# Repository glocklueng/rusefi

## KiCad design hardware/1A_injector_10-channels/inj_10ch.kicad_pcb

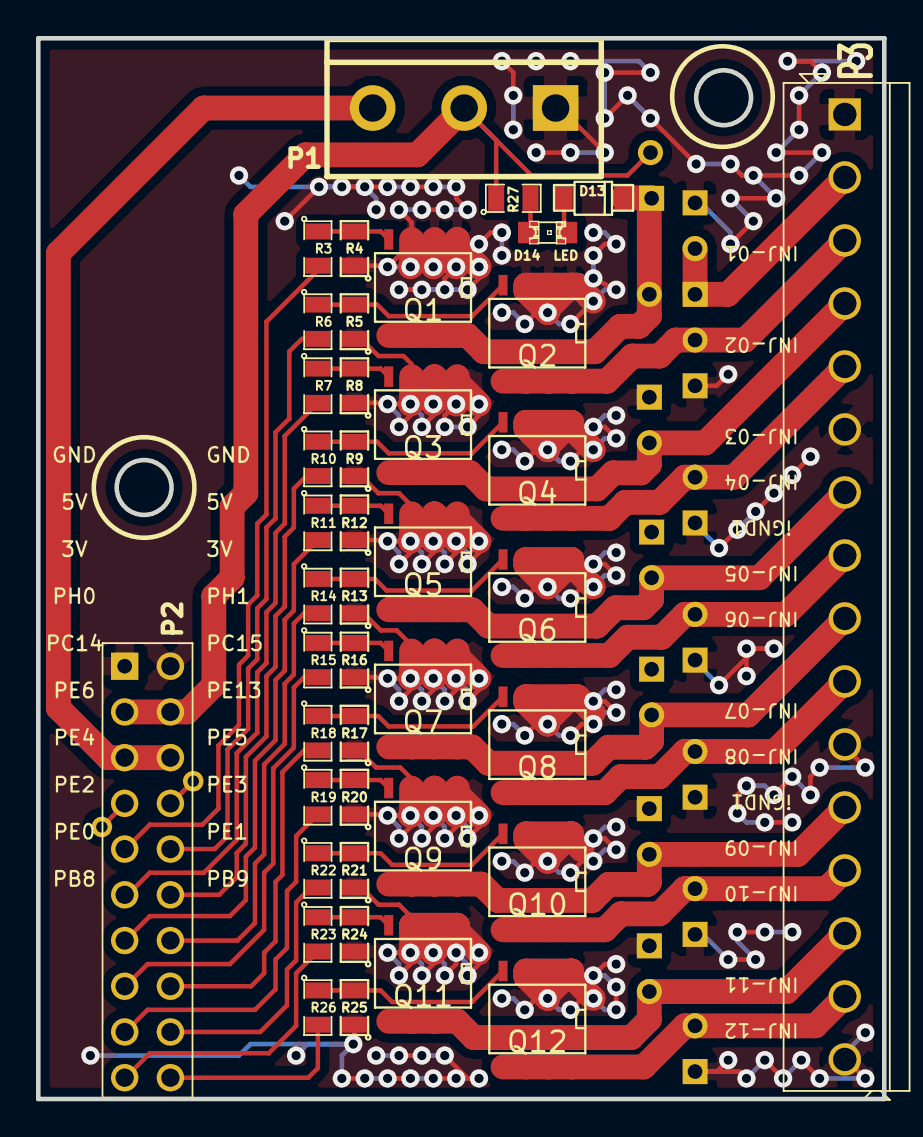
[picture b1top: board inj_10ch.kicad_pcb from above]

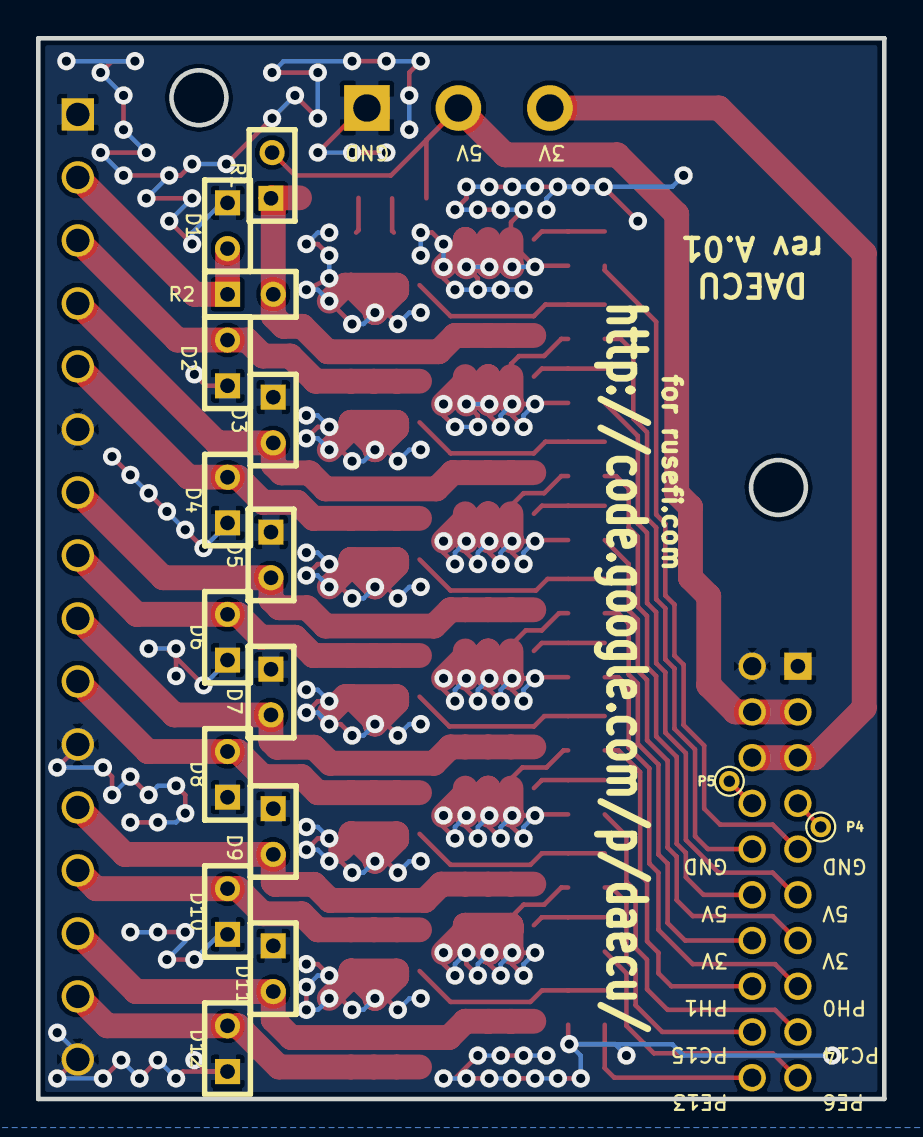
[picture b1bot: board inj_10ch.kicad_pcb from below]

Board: 2 copper layers, 47.0 x 58.9 mm, 58 parts (16 on the bottom side), 44 nets.

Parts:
D1, D2, D3, D4, D5, D6, D7, D8, D9, D10, D11, D12: DIODE; SIL-2
D13: DIODE; SOD-123
D14: LED; LED-0805
P1: CONN_3; bornier3
P2: CONN_10X2; pin_array_10x2
P3: CONN_16; SIL-16_3.5MM
P4, P5: CONN_1; PINTST
Q1, Q2, Q3, Q4, Q5, Q6, Q7, Q8, Q9, Q10, Q11, Q12: OVP_DRIVER; SO8E_ST
R1: OPT; SIL-2
R2: 0R; SIL-2
R3, R6, R7, R10, R11, R14, R15, R18, R19, R22, R23, R26: 20R; SM0805
R4, R5, R8, R9, R12, R13, R16, R17, R20, R21, R24, R25, R27: 1K; SM0805

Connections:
/3V: P1.3, P2.5, P2.6
/5V: P1.2, P2.3, P2.4, R1.2, R27.1
/INJ-01: D13.2, Q1.2, R1.1, R2.2
/INJ-01_2: D1.2, P3.2, R2.1
/INJ-01_5V: P2.9, R3.2
/INJ-02: D2.2, P3.3, Q2.2
/INJ-02_5V: P2.10, R6.2
/INJ-03: D3.2, P3.4, Q3.2
/INJ-03_5V: P2.11, R7.2
/INJ-04: D4.2, P3.5, Q4.2
/INJ-04_5V: P2.12, R10.2
/INJ-05: D5.2, P3.7, Q5.2
/INJ-05_5V: P2.13, R11.2
/INJ-06: D6.2, P3.8, Q6.2
/INJ-06_5V: P2.14, R14.2
/INJ-07: D7.2, P3.9, Q7.2
/INJ-07_5V: P2.15, R15.2
/INJ-08: D8.2, P3.10, Q8.2
/INJ-08_5V: P2.16, R18.2
/INJ-09: D9.2, P3.12, Q9.2
/INJ-09_5V: P2.17, R19.2
/INJ-10: D10.2, P3.13, Q10.2
/INJ-10_5V: P2.18, R22.2
/INJ-11: D11.2, P3.14, Q11.2
/INJ-11_5V: P2.19, R23.2
/INJ-12: D12.2, P3.15, Q12.2
/INJ-12_5V: P2.20, R26.2
/PH0: P2.7, P4.1
/PH1: P2.8, P5.1
GND: D1.1, D2.1, D3.1, D4.1, D5.1, D6.1, D7.1, D8.1, D9.1, D10.1, D11.1, D12.1, P1.1, P2.1, P2.2, P3.1, P3.6, P3.11, P3.16, Q1.3, Q2.3, Q3.3, Q4.3, Q5.3, Q6.3, Q7.3, Q8.3, Q9.3, Q10.3, Q11.3, Q12.3, R4.1, R5.1, R8.1, R9.1, R12.1, R13.1, R16.1, R17.1, R20.1, R21.1, R24.1, R25.1
unnamed: Q3.1, R7.1, R8.2
unnamed: Q2.1, R5.2, R6.1
unnamed: Q1.1, R3.1, R4.2
unnamed: Q6.1, R13.2, R14.1
unnamed: Q11.1, R23.1, R24.2
unnamed: Q4.1, R9.2, R10.1
unnamed: Q5.1, R11.1, R12.2
unnamed: Q9.1, R19.1, R20.2
unnamed: Q10.1, R21.2, R22.1
unnamed: Q12.1, R25.2, R26.1
unnamed: Q8.1, R17.2, R18.1
unnamed: D14.1, R27.2
unnamed: Q7.1, R15.1, R16.2
unnamed: D13.1, D14.2

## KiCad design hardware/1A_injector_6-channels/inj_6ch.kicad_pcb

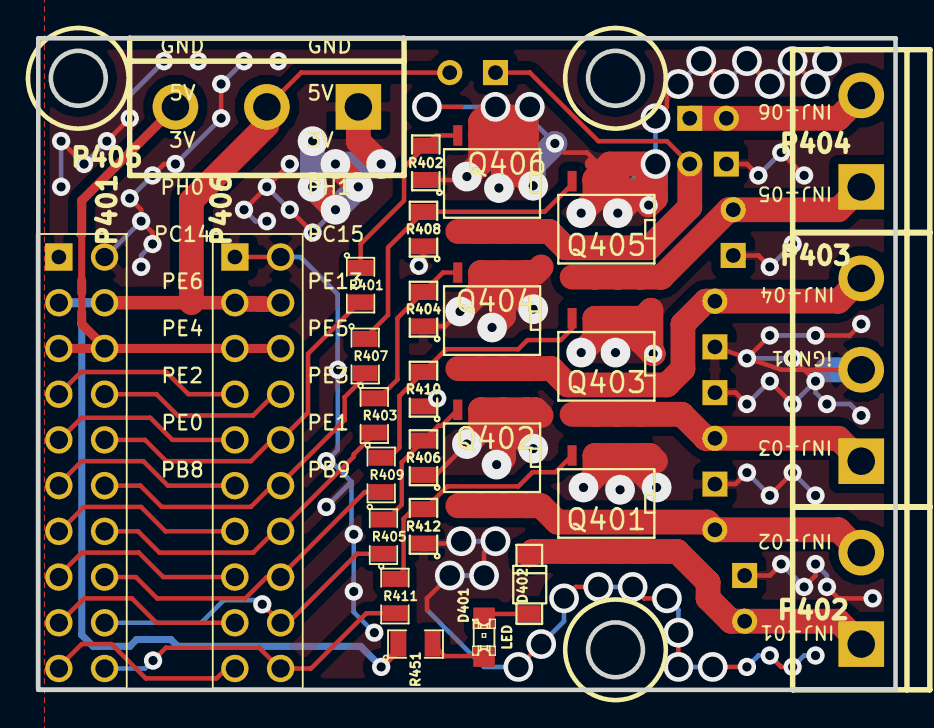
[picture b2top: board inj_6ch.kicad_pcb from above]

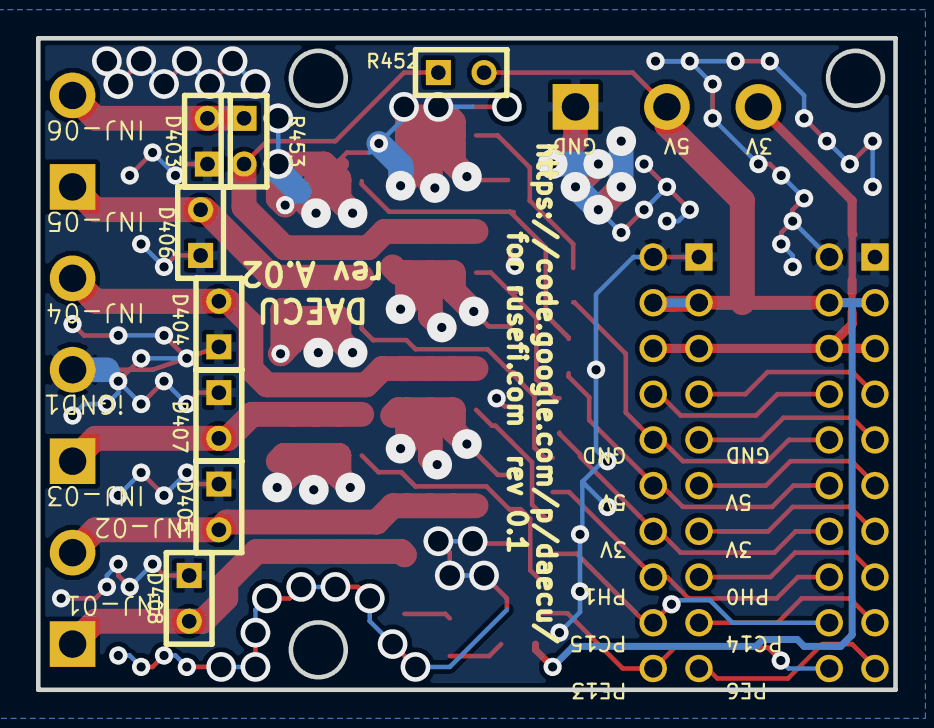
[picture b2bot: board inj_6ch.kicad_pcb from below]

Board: 2 copper layers, 47.6 x 36.2 mm, 35 parts (8 on the bottom side), 32 nets.

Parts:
D401: LED; LED-0805
D402: DIODE; SOD-123
D403, D404, D405, D406, D407, D408: DIODE; SIL-2
P401: HEADER_10X2; pin_array_10x2
P402, P404: CONN_2; bornier2
P403, P405: CONN_3; bornier3
P406: CONN_10X2; pin_array_10x2
Q401, Q402, Q403, Q404, Q405, Q406: OVP_DRIVER; SO8E_ST
R401, R403, R405, R407, R409, R411: 20R; SM0805
R402, R404, R406, R408, R410, R412, R451: 1K; SM0805
R452: OPT; SIL-2
R453: 0R; SIL-2

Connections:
/3V: P401.5, P401.6, P405.3, P406.5, P406.6
/5V: P401.3, P401.4, P405.2, P406.3, P406.4, R451.1, R452.2
/INJ-01: D402.2, D408.2, P402.1, Q401.2
/INJ-01_5V: P401.20, P406.20, R411.2
/INJ-02: D405.2, P402.2, Q402.2
/INJ-02_5V: P401.18, P406.18, R405.2
/INJ-03: D407.2, P403.1, Q403.2
/INJ-03_5V: P401.16, P406.16, R409.2
/INJ-04: D404.2, P403.3, Q404.2
/INJ-04_5V: P401.14, P406.14, R403.2
/INJ-05: D406.2, P404.1, Q405.2
/INJ-05_5V: P401.12, P406.12, R407.2
/INJ-06: Q406.2, R452.1, R453.2
/INJ-06_2: D403.2, P404.2, R453.1
/INJ-06_5V: P401.10, P406.10, R401.2
/PB8: P401.19, P406.19
/PC14: P401.9, P406.9
/PE0: P401.17, P406.17
/PE2: P401.15, P406.15
/PE4: P401.13, P406.13
/PE6: P401.11, P406.11
/PH0: P401.7, P406.7
/PH1: P401.8, P406.8
GND: D403.1, D404.1, D405.1, D406.1, D407.1, D408.1, P401.1, P401.2, P403.2, P405.1, P406.1, P406.2, Q401.3, Q402.3, Q403.3, Q404.3, Q405.3, Q406.3, R402.1, R404.1, R406.1, R408.1, R410.1, R412.1
unnamed: D401.1, R451.2
unnamed: D401.2, D402.1
unnamed: Q401.1, R411.1, R412.2
unnamed: Q402.1, R405.1, R406.2
unnamed: Q403.1, R409.1, R410.2
unnamed: Q404.1, R403.1, R404.2
unnamed: Q406.1, R401.1, R402.2
unnamed: Q405.1, R407.1, R408.2

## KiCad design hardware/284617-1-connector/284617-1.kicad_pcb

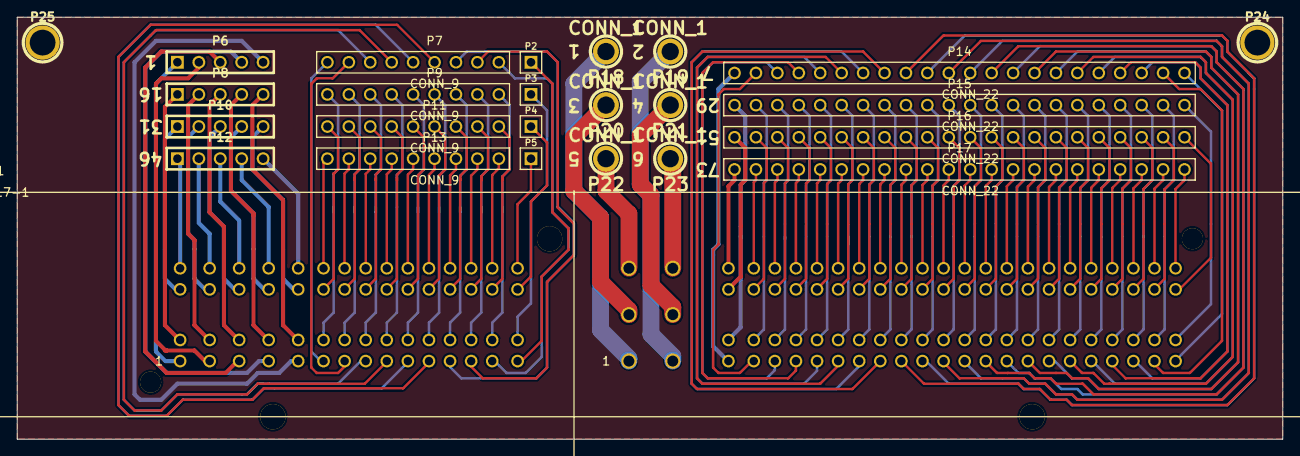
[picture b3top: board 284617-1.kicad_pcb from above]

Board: 2 copper layers, 150.0 x 50.0 mm, 25 parts (0 on the bottom side), 155 nets.

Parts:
P1: 284617-1
P2, P3, P4, P5: CONN_1; PIN_ARRAY_1
P6, P8, P10, P12: CONN_5; PIN_ARRAY_5x1
P7, P9, P11, P13: CONN_9; PIN_ARRAY_9x1
P14, P15, P16, P17: CONN_22; PIN_ARRAY_22x1
P18, P19, P20, P21, P22, P23: CONN_1; 1pin(m)
P24, P25: CONN_1; 1pin

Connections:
/GND: P24.1, P25.1
unnamed: P1.94, P15.6
unnamed: P1.108, P15.20
unnamed: P1.107, P15.19
unnamed: P1.106, P15.18
unnamed: P1.105, P15.17
unnamed: P1.104, P15.16
unnamed: P1.103, P15.15
unnamed: P1.102, P15.14
unnamed: P1.101, P15.13
unnamed: P1.100, P15.12
unnamed: P1.99, P15.11
unnamed: P1.98, P15.10
unnamed: P1.97, P15.9
unnamed: P1.96, P15.8
unnamed: P1.95, P15.7
unnamed: P1.109, P15.21
unnamed: P1.93, P15.5
unnamed: P1.92, P15.4
unnamed: P1.91, P15.3
unnamed: P1.90, P15.2
unnamed: P1.89, P15.1
unnamed: P1.88, P14.22
unnamed: P1.87, P14.21
unnamed: P1.86, P14.20
unnamed: P1.85, P14.19
unnamed: P1.84, P14.18
unnamed: P1.83, P14.17
unnamed: P1.82, P14.16
unnamed: P1.81, P14.15
unnamed: P1.80, P14.14
unnamed: P1.123, P16.13
unnamed: P1.137, P17.5
unnamed: P1.136, P17.4
unnamed: P1.135, P17.3
unnamed: P1.134, P17.2
unnamed: P1.133, P17.1
unnamed: P1.132, P16.22
unnamed: P1.131, P16.21
unnamed: P1.130, P16.20
unnamed: P1.129, P16.19
unnamed: P1.128, P16.18
unnamed: P1.127, P16.17
unnamed: P1.126, P16.16
unnamed: P1.125, P16.15
unnamed: P1.124, P16.14
unnamed: P1.79, P14.13
unnamed: P1.122, P16.12
unnamed: P1.121, P16.11
unnamed: P1.120, P16.10
unnamed: P1.119, P16.9
unnamed: P1.118, P16.8
unnamed: P1.117, P16.7
unnamed: P1.116, P16.6
unnamed: P1.115, P16.5
unnamed: P1.114, P16.4
unnamed: P1.113, P16.3
unnamed: P1.112, P16.2
unnamed: P1.111, P16.1
unnamed: P1.110, P15.22
unnamed: P1.138, P17.6
unnamed: P1.78, P14.12
unnamed: P1.77, P14.11
unnamed: P1.76, P14.10
unnamed: P1.75, P14.9
unnamed: P1.74, P14.8
unnamed: P1.73, P14.7
unnamed: P1.72, P14.6
unnamed: P1.71, P14.5
unnamed: P1.70, P14.4
unnamed: P1.69, P14.3
unnamed: P1.68, P14.2
unnamed: P1.67, P14.1
unnamed: P1.154, P17.22
unnamed: P1.144, P17.12
unnamed: P1.153, P17.21
unnamed: P1.143, P17.11
unnamed: P1.152, P17.20
unnamed: P1.142, P17.10
unnamed: P1.151, P17.19
unnamed: P1.141, P17.9
unnamed: P1.150, P17.18
unnamed: P1.140, P17.8
unnamed: P1.147, P17.15
unnamed: P1.149, P17.17
unnamed: P1.139, P17.7
unnamed: P1.148, P17.16
unnamed: P1.146, P17.14
unnamed: P1.145, P17.13
unnamed: P1.62, P19.1
unnamed: P1.61, P18.1
unnamed: P1.45, P4.1
unnamed: P1.63, P20.1
unnamed: P1.66, P23.1
unnamed: P1.65, P22.1
unnamed: P1.64, P21.1
unnamed: P1.1, P6.1
unnamed: P1.59, P13.9
unnamed: P1.49, P12.4
unnamed: P1.60, P5.1
unnamed: P1.43, P11.8
unnamed: P1.33, P10.3
unnamed: P1.23, P9.3
unnamed: P1.13, P7.8
unnamed: P1.52, P13.2
unnamed: P1.42, P11.7
unnamed: P1.32, P10.2
unnamed: P1.22, P9.2
unnamed: P1.12, P7.7
unnamed: P1.51, P13.1
unnamed: P1.41, P11.6
unnamed: P1.31, P10.1
unnamed: P1.21, P9.1
unnamed: P1.11, P7.6
unnamed: P1.53, P13.3
unnamed: P1.50, P12.5
unnamed: P1.40, P11.5
unnamed: P1.30, P3.1
unnamed: P1.20, P8.5
unnamed: P1.10, P7.5
unnamed: P1.9, P7.4
unnamed: P1.8, P7.3
unnamed: P1.7, P7.2
unnamed: P1.6, P7.1
unnamed: P1.5, P6.5
unnamed: P1.4, P6.4
unnamed: P1.3, P6.3
unnamed: P1.2, P6.2
unnamed: P1.46, P12.1
unnamed: P1.39, P11.4
unnamed: P1.29, P9.9
unnamed: P1.19, P8.4
unnamed: P1.48, P12.3
unnamed: P1.38, P11.3
unnamed: P1.28, P9.8
unnamed: P1.18, P8.3
unnamed: P1.57, P13.7
unnamed: P1.47, P12.2
unnamed: P1.37, P11.2
unnamed: P1.27, P9.7
unnamed: P1.17, P8.2
unnamed: P1.56, P13.6
unnamed: P1.58, P13.8
unnamed: P1.36, P11.1
unnamed: P1.26, P9.6
unnamed: P1.16, P8.1
unnamed: P1.55, P13.5
unnamed: P1.35, P10.5
unnamed: P1.25, P9.5
unnamed: P1.15, P2.1
unnamed: P1.54, P13.4
unnamed: P1.44, P11.9
unnamed: P1.34, P10.4
unnamed: P1.24, P9.4
unnamed: P1.14, P7.9

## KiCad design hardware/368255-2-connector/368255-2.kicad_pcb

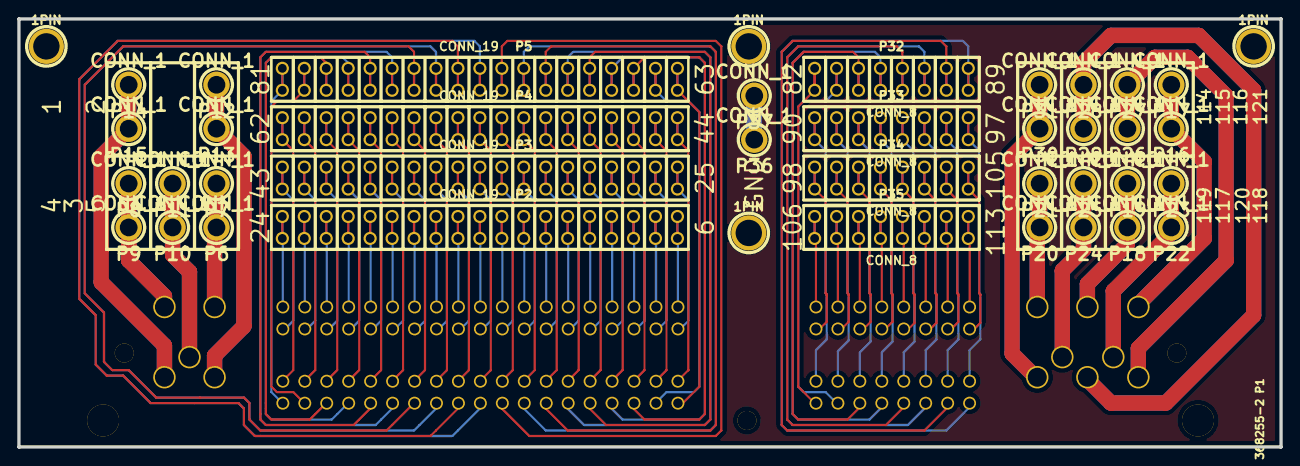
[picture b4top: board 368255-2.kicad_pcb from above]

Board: 2 copper layers, 146.1 x 49.5 mm, 41 parts (0 on the bottom side), 122 nets.

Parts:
1PIN, 1PIN#2, 1PIN#3, 1PIN#4: P***; 1pin
P1: 368255-2
P2, P3, P4, P5: CONN_19; 19dpad
P6, P7, P8, P9, P10, P11, P12, P13, P14, P15, P16, P17, P18, P19, P20, P21, P22, P23, P24, P25, P26, P27, P28, P29, P30, P31, P36, P37: CONN_1; 1pin(m)
P32, P33, P34, P35: CONN_8; 8dpad

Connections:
GND: P36.1, P37.1
unnamed: P1.22, P2.17
unnamed: P1.34, P3.10
unnamed: P1.33, P3.9
unnamed: P1.32, P3.8
unnamed: P1.31, P3.7
unnamed: P1.30, P3.6
unnamed: P1.29, P3.5
unnamed: P1.28, P3.4
unnamed: P1.27, P3.3
unnamed: P1.26, P3.2
unnamed: P1.25, P3.1
unnamed: P1.24, P2.19
unnamed: P1.23, P2.18
unnamed: P1.35, P3.11
unnamed: P1.21, P2.16
unnamed: P1.20, P2.15
unnamed: P1.19, P2.14
unnamed: P1.18, P2.13
unnamed: P1.17, P2.12
unnamed: P1.16, P2.11
unnamed: P1.15, P2.10
unnamed: P1.14, P2.9
unnamed: P1.13, P2.8
unnamed: P1.12, P2.7
unnamed: P1.11, P2.6
unnamed: P1.10, P2.5
unnamed: P1.48, P4.5
unnamed: P1.60, P4.17
unnamed: P1.59, P4.16
unnamed: P1.58, P4.15
unnamed: P1.57, P4.14
unnamed: P1.56, P4.13
unnamed: P1.55, P4.12
unnamed: P1.54, P4.11
unnamed: P1.53, P4.10
unnamed: P1.52, P4.9
unnamed: P1.51, P4.8
unnamed: P1.50, P4.7
unnamed: P1.49, P4.6
unnamed: P1.9, P2.4
unnamed: P1.47, P4.4
unnamed: P1.46, P4.3
unnamed: P1.45, P4.2
unnamed: P1.44, P4.1
unnamed: P1.43, P3.19
unnamed: P1.42, P3.18
unnamed: P1.41, P3.17
unnamed: P1.40, P3.16
unnamed: P1.39, P3.15
unnamed: P1.38, P3.14
unnamed: P1.37, P3.13
unnamed: P1.36, P3.12
unnamed: P1.94, P33.5
unnamed: P1.106, P35.1
unnamed: P1.105, P34.8
unnamed: P1.104, P34.7
unnamed: P1.103, P34.6
unnamed: P1.102, P34.5
unnamed: P1.101, P34.4
unnamed: P1.100, P34.3
unnamed: P1.99, P34.2
unnamed: P1.98, P34.1
unnamed: P1.97, P33.8
unnamed: P1.96, P33.7
unnamed: P1.95, P33.6
unnamed: P1.107, P35.2
unnamed: P1.93, P33.4
unnamed: P1.92, P33.3
unnamed: P1.91, P33.2
unnamed: P1.90, P33.1
unnamed: P1.89, P32.8
unnamed: P1.88, P32.7
unnamed: P1.87, P32.6
unnamed: P1.86, P32.5
unnamed: P1.85, P32.4
unnamed: P1.84, P32.3
unnamed: P1.83, P32.2
unnamed: P1.82, P32.1
unnamed: P1.117, P24.1, P25.1
unnamed: P1.8, P2.3
unnamed: P1.7, P2.2
unnamed: P1.6, P2.1
unnamed: P1.120, P18.1, P19.1
unnamed: P1.118, P22.1, P23.1
unnamed: P1.61, P4.18
unnamed: P1.116, P26.1, P27.1
unnamed: P1.115, P28.1, P29.1
unnamed: P1.114, P30.1, P31.1
unnamed: P1.113, P35.8
unnamed: P1.112, P35.7
unnamed: P1.111, P35.6
unnamed: P1.110, P35.5
unnamed: P1.109, P35.4
unnamed: P1.108, P35.3
unnamed: P1.121, P16.1, P17.1
unnamed: P1.119, P20.1, P21.1
unnamed: P1.74, P5.12
unnamed: P1.81, P5.19
unnamed: P1.80, P5.18
unnamed: P1.79, P5.17
unnamed: P1.78, P5.16
unnamed: P1.77, P5.15
unnamed: P1.76, P5.14
unnamed: P1.75, P5.13
unnamed: P1.73, P5.11
unnamed: P1.72, P5.10
unnamed: P1.71, P5.9
unnamed: P1.70, P5.8
unnamed: P1.69, P5.7
unnamed: P1.68, P5.6
unnamed: P1.67, P5.5
unnamed: P1.66, P5.4
unnamed: P1.65, P5.3
unnamed: P1.64, P5.2
unnamed: P1.63, P5.1
unnamed: P1.62, P4.19
unnamed: P1.5, P6.1, P7.1
unnamed: P1.4, P8.1, P9.1
unnamed: P1.3, P10.1, P11.1
unnamed: P1.2, P12.1, P13.1
unnamed: P1.1, P14.1, P15.1

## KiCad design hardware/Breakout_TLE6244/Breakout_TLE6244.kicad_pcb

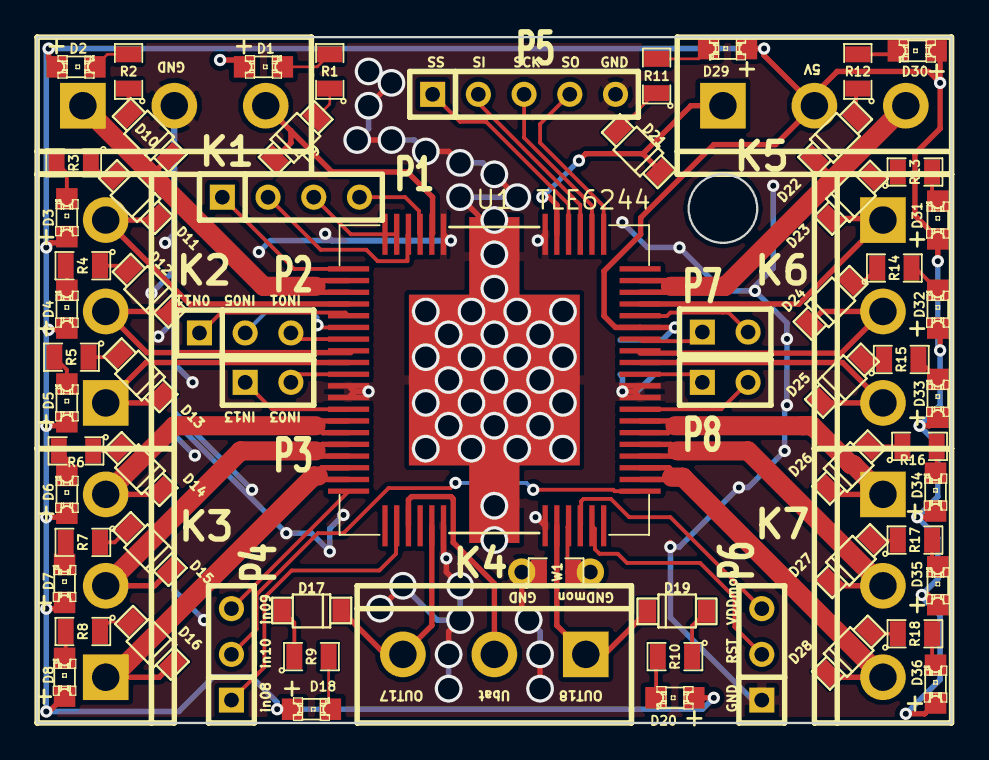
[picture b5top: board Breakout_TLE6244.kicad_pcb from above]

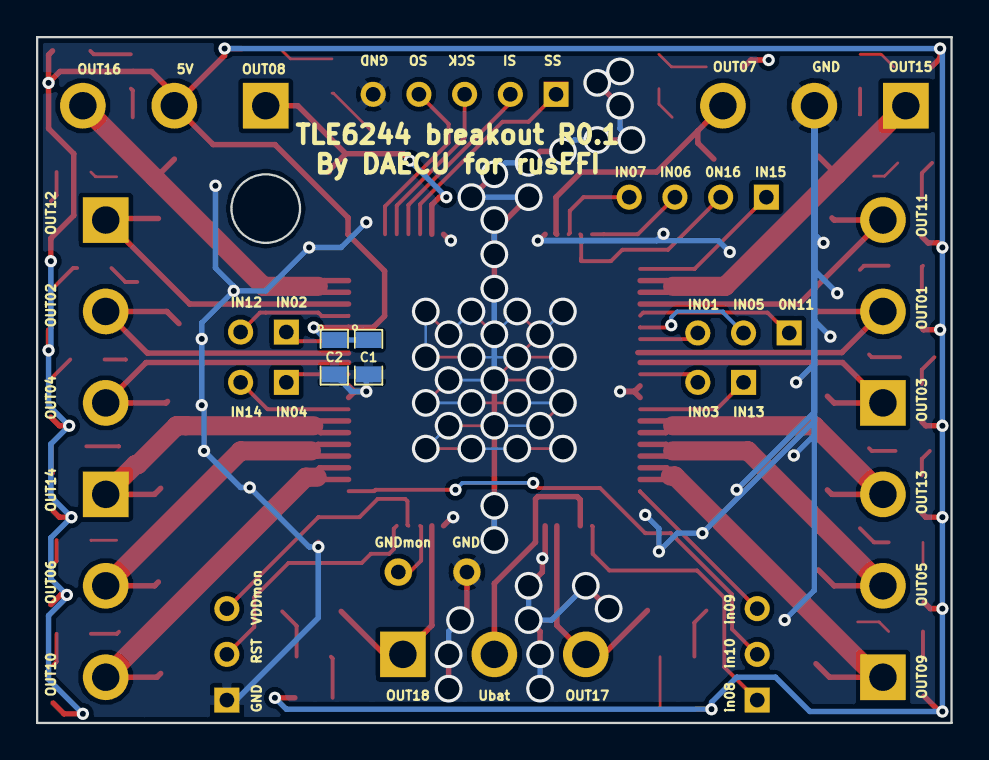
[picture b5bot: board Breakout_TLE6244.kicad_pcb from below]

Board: 4 copper layers, 50.8 x 38.1 mm, 73 parts (2 on the bottom side), 80 nets.

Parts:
C1: 1uF; SM0805
C2: .01uF; SM0805
D1, D2, D3, D4, D5, D6, D7, D8, D18, D20, D29, D30, D31, D32, D33, D34, D35, D36: LED-red; LED-0805_A
D9, D10, D11, D12, D13, D14, D15, D16, D17, D19, D21, D22, D23, D24, D25, D26, D27, D28: DIODE; SOD-123
K1, K2, K3, K4, K5, K6, K7: CONN_3; bornier3
P1: CONN_4; SIL-4
P2, P4, P6: CONN_3; SIL-3
P3, P7, P8: CONN_2; SIL-2
P5: CONN_5; SIL-5
R1, R2, R3, R4, R5, R6, R7, R8, R9, R10, R11, R12, R13, R14, R15, R16, R17, R18: 1K; SM0805
U1: TLE6244; HiQUAD64
W1: TEST; SM0805_jumper

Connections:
/5v: C1.1, C2.1, D1.1, D2.1, D3.1, D4.1, D5.1, D6.1, D7.1, D8.1, D18.1, D20.1, D29.1, D30.1, D31.1, D32.1, D33.1, D34.1, D35.1, D36.1, K5.2, U1.47
/GNDmon: U1.29, W1.2
/RST: P6.2, U1.31
/SCK: P5.3, U1.54
/SI: P5.2, U1.55
/SO: P5.4, U1.53
/SS: P5.1, U1.56
/Ubatt: K4.2, U1.23
/VDDmon: P6.3, U1.30
/in01: P2.3, U1.7
/in02: P7.1, U1.46
/in03: P3.2, U1.10
/in04: P8.1, U1.43
/in05: P2.2, U1.6
/in06: P1.3, U1.63, U1.64
/in07: P1.4, U1.61
/in08: P4.1, U1.22
/in09: P4.3, U1.20
/in10: P4.2, U1.33
/in11: P2.1, U1.5
/in12: P7.2, U1.48
/in13: P3.1, U1.13
/in14: P8.2, U1.40
/in15: P1.1, U1.1
/in16: P1.2, U1.62
/out01: D12.2, K2.2, U1.8
/out02: D24.2, K6.2, U1.45
/out03: D13.2, K2.1, U1.9
/out04: D25.2, K6.3, U1.44
/out05: D15.2, K3.2, U1.16, U1.17
/out06: D27.2, K7.2, U1.36, U1.37
/out07: D9.2, K1.3, U1.60
/out08: D21.2, K5.1, U1.57
/out09: D16.2, K3.1, U1.18, U1.19
/out10: D28.2, K7.3, U1.34, U1.35
/out11: D11.2, K2.3, U1.4
/out12: D23.2, K6.1, U1.49
/out13: D14.2, K3.3, U1.14, U1.15
/out14: D26.2, K7.1, U1.38, U1.39
/out15: D10.2, K1.1, U1.2, U1.3
/out16: D22.2, K5.3, U1.50, U1.51
/out17: D17.2, K4.3, U1.25
/out18: D19.2, K4.1, U1.28
GND: C1.2, C2.2, K1.2, P5.5, P6.1, U1.11, U1.12, U1.26, U1.27, U1.41, U1.42, U1.58, U1.59, U1.slug, W1.1
unnamed: D9.1, R1.1
unnamed: D21.1, R11.1
unnamed: D29.2, R11.2
unnamed: D1.2, R1.2
unnamed: D17.1, R9.1
unnamed: D18.2, R9.2
unnamed: D3.2, R3.2
unnamed: D11.1, R3.1
unnamed: D22.1, R12.1
unnamed: D30.2, R12.2
unnamed: D2.2, R2.2
unnamed: D10.1, R2.1
unnamed: D27.1, R17.1
unnamed: D28.1, R18.1
unnamed: D36.2, R18.2
unnamed: D35.2, R17.2
unnamed: D26.1, R16.1
unnamed: D34.2, R16.2
unnamed: D25.1, R15.1
unnamed: D33.2, R15.2
unnamed: D19.1, R10.1
unnamed: D20.2, R10.2
unnamed: D5.2, R5.2
unnamed: D7.2, R7.2
unnamed: D15.1, R7.1
unnamed: D14.1, R6.1
unnamed: D6.2, R6.2
unnamed: D13.1, R5.1
unnamed: D12.1, R4.1
unnamed: D4.2, R4.2
unnamed: D24.1, R14.1
unnamed: D32.2, R14.2
unnamed: D23.1, R13.1
unnamed: D31.2, R13.2
unnamed: D16.1, R8.1
unnamed: D8.2, R8.2

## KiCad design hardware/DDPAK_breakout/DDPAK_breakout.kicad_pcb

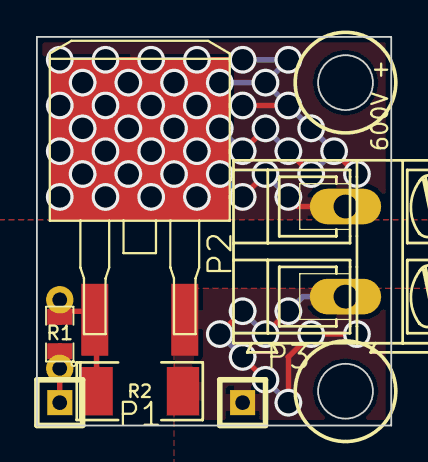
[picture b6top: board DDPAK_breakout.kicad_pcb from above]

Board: 2 copper layers, 19.7 x 21.6 mm, 6 parts (0 on the bottom side), 4 nets.

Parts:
P1, P3: CONN_1; SIL-1
P2: CONN_2; AK300-2
Q1: IRGS14C40L; m-pad-2.1-TO-263AB
R1: 1K; SM0805_jumper
R2: 100K; SM2010

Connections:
/GND: P2.2, P3.1, Q1.3, R2.2
/HV: P2.1, Q1.2
/SIG: P1.1, R1.1
/SIG2: Q1.1, R1.2, R2.1
